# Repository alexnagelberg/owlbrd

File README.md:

# OwlBrd
This board was made to supersede EasyBrd but it has a lot more to it so for cost or complexity, you can pick and choose what you want. The only section needed to drive 8 spools is the core section, ideally with distance sensors as well. Most of these parts can be found [in the US] on Amazon/Digikey and should be widely available and low cost and swappable with different manufacturers, the one exception being the optional TCA9548A breakout which only works with Adafruit's (maybe in future I'll add another row of pins to allow the hiletgo variants, but some workarounds can be done).

All the boards can be soldered either directly down or put down a set of headers so the boards can be removed/replaced. I would maybe take care with the TMC drivers as there's a resistor under each, but you could also solder the resistors on the bottom side if there's concerns of heat/proximity without a header -- probably shouldn't be an issue at all.

## BOM (split by functionality)

### Misc (listed again throughout sections)
 - Dupont male/female headers ([Amazon Affiliate](https://amzn.to/3ps0VLI))
 - Resistors - 1k, 10k, 2.37k, 4.7k used throughout (kit: [Amazon affiliate](https://amzn.to/3c7XxCF))
 - Ceramic capacitors: 0.33uF, 0.1uF used in ERCF/heater (kit: [Amazon affiliate](https://amzn.to/3wbLxqx))
 - Electrolytic capacitors: 100uF 25v used in ERCF/rewinder (kit: [Amazon affiliate](https://amzn.to/3Qs2sNM))
 - JST-XH connectors: 2-pin, 3-pin, 4-pin (kit: [Amazon affiliate](https://amzn.to/3AnAbBp))
 - Screw terminals for power/heater ([Amazon affiliate](https://amzn.to/3T8kE0O))

### Core (Rewind Stepper + Clutches)
- Raspberry Pi Pico ([[Digikey](https://www.digikey.com/en/products/detail/raspberry-pi/SC0915/13624793)] headers are optional)
- BTT TMC2209 x1 ([[Amazon affiliate](https://amzn.to/3prqGvD)] headers encouraged, note that UART is currently wired to the 4th pin and some like FYSETC use the 5th pin. You might be able to resolve this with a jumper on the pins on top?)
- 74HC238 DIP ([Amazon affiliate](https://amzn.to/3PAAPkm)) for clutch (addresses 8 pins using 3 GPIO)
- ULN2803A DIP ([Amazon affiliate](https://amzn.to/3QPcatl)) for clutch (drives 8 clutches using one IC)
- Screw terminal for power
- Resistors: 10k (x1), 1k (x1)
- JST-XH 2 pin female (x8) for clutches
- JST-XH 4 pin female (x2) for rewinder steppers
- Electrolytic capacitor: 100uF 25v

### Distance Sensors
- Adafruit TCA9548A ([Amazon affiliate](https://amzn.to/3wdmtQd) or [adafruit](https://www.adafruit.com/product/2717)) breakout (headers optional, cheaper generics available but one side is slightly wider by like 2.5mm -- might be able to rig something to fit it or could use wires)
- JST-XH 4 pin female (x8) for each sensor

### ERCF
- BTT TMC2209 x2 ([[Amazon affiliate](https://amzn.to/3prqGvD)] headers encouraged, note that UART is currently wired to the 4th pin and some like FYSETC use the 5th pin. You might be able to resolve this with a jumper on the pins on top?)
- L7805CV ([Amazon affiliate](https://amzn.to/3zYoTTM)) 5v linear regulator (probably plenty of substitutions for this but should be readily available -- any 5v regulator with same pinout should work) for supplying 5v power on board
- Resistors: 10k (x2)
- Ceramic capacitors: 0.33uF x1, 0.1uF x1
- Electrolytic capacitors: 100uF 25v (x2)
- JST-XH 3 pin female (x4) for servo, encoder, endstop, and optional neopixel/misc
- JST-XH 4 pin female (x2) for selector/gear steppers

### Heater
- IRLB8721PBF ([Amazon affiliate](https://amzn.to/3A3fAC1)) MOSFET (probably lots of substitutable options but should be readily available)
- BAV99 SMD ([[Amazon affiliate](https://amzn.to/3Pub5Gj)] only surface mount component -- shouldn't be too difficult to solder or need anything special, needed for thermistor)
- Screw terminal (or connector of your choice) for heater
- Resistors: 2.37k (x2), 4.7k (x1)
- Ceramic capacitor: 0.1uF
- JST-XH 2 pin female (for thermistor)

### UART
There's a breakout for UART with power for pi. If you use UART, and don't connect pico to USB, you'll want to put a header and jumper on J29 Ext Power so that it powers the pico from the 5v regulator. Install the 0.33uF and 0.1uF capacitors and L7805CV from ERCF section to get 5v power if needed.

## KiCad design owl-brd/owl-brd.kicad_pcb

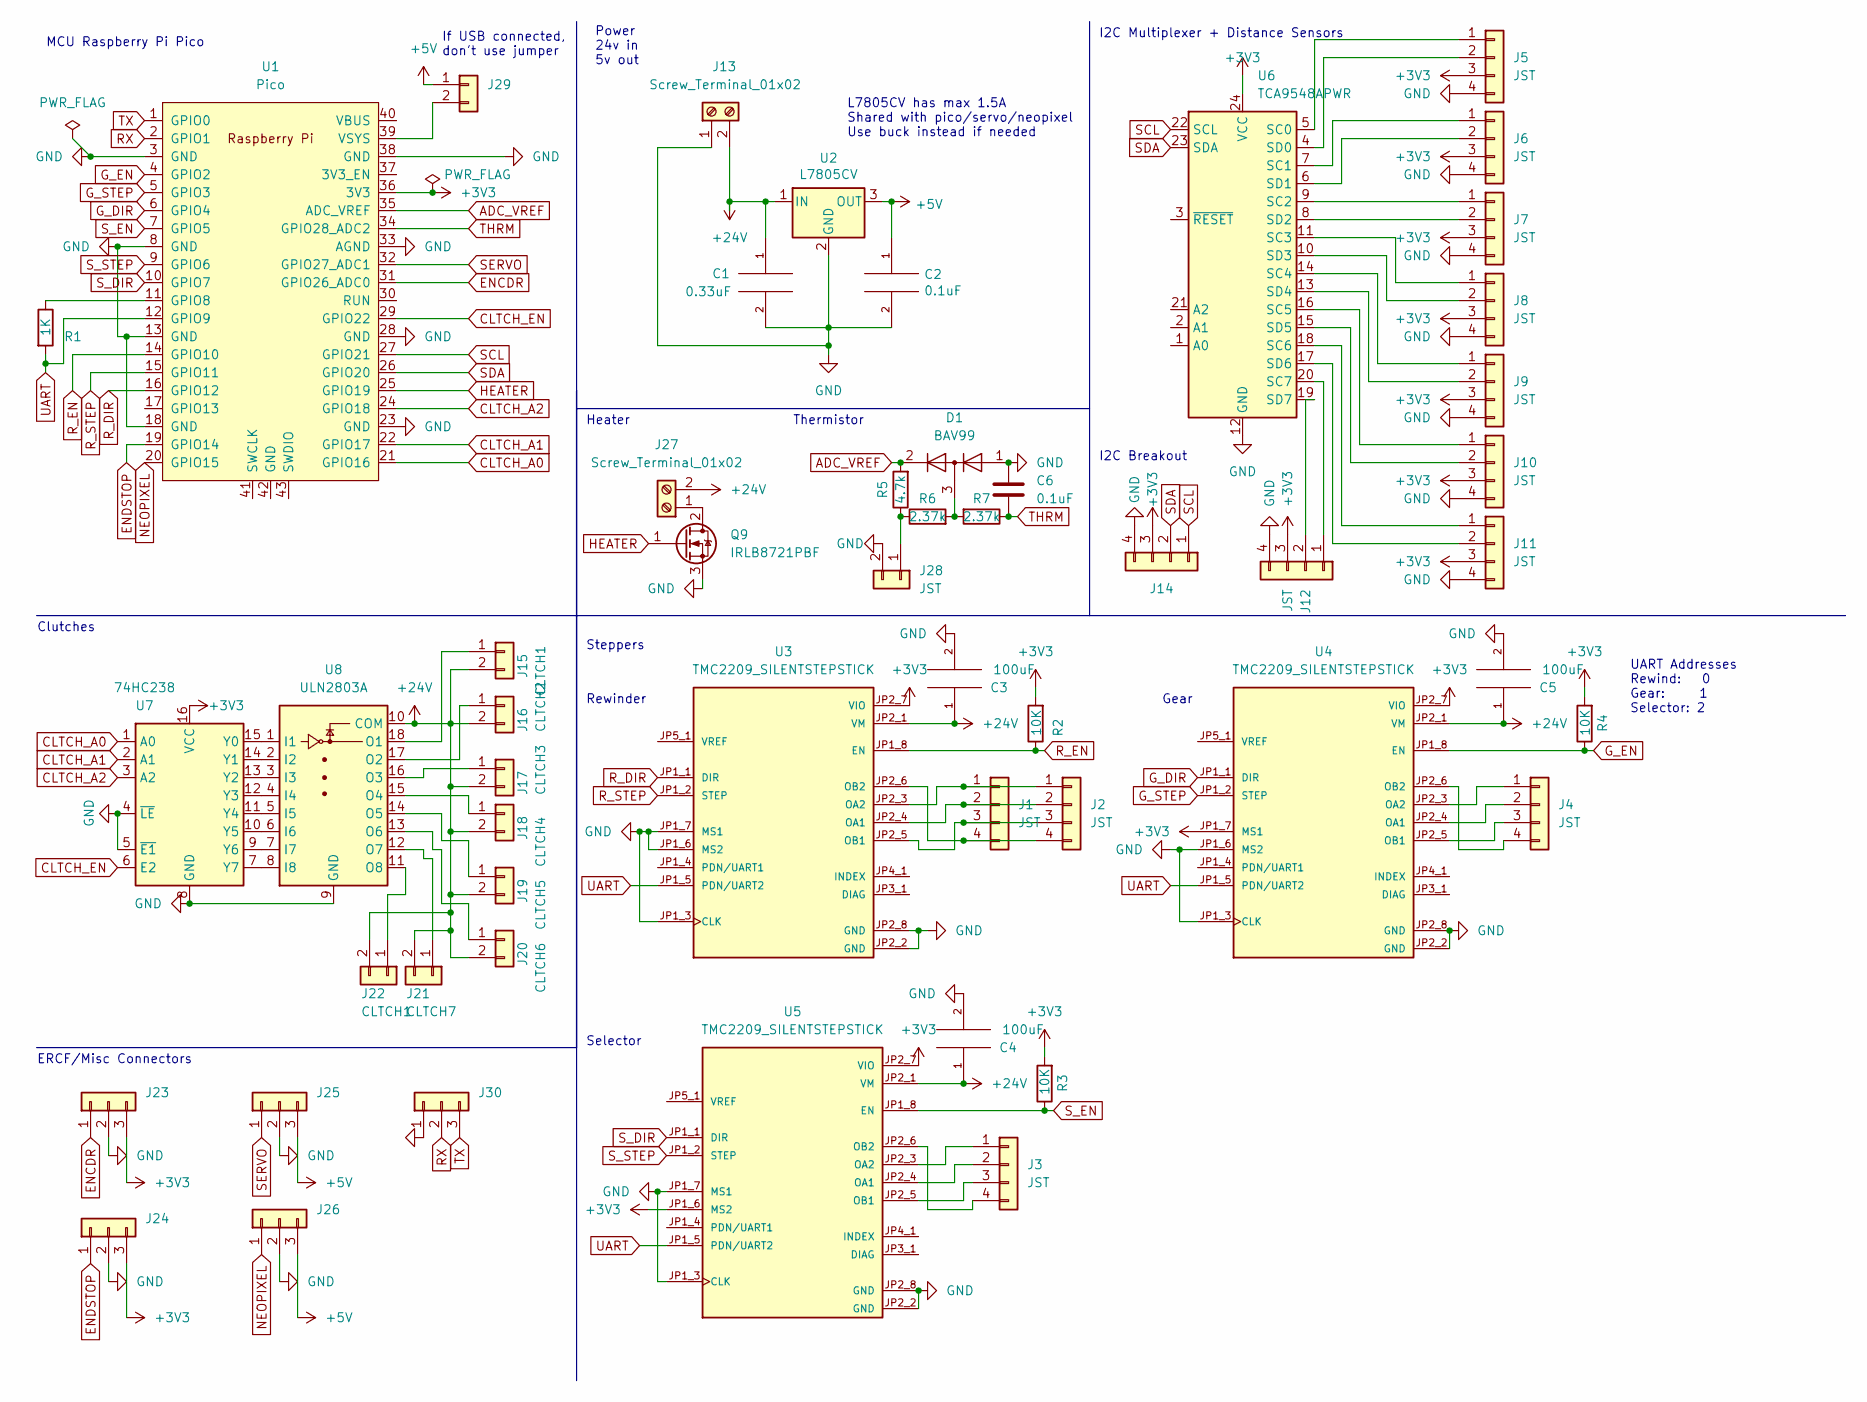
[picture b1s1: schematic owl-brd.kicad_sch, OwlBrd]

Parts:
C1: 0.33uF; C_Disc_D3.0mm_W1.6mm_P2.50mm
C2, C6: 0.1uF; C_Disc_D3.0mm_W1.6mm_P2.50mm
C3, C4, C5: 100uF; CP_Radial_D8.0mm_P3.50mm
D1: BAV99; SOT-23
J1, J2, J3, J4, J5, J6, J7, J8, J9, J10, J11, J12: JST; JST_XH_B4B-XH-A_1x04_P2.50mm_Vertical
J13, J27: Screw_Terminal_01x02; TerminalBlock_bornier-2_P5.08mm
J14, J29, J30: (no value)
J15, J22: CLTCH1; JST_XH_B2B-XH-A_1x02_P2.50mm_Vertical
J16: CLTCH2; JST_XH_B2B-XH-A_1x02_P2.50mm_Vertical
J17: CLTCH3; JST_XH_B2B-XH-A_1x02_P2.50mm_Vertical
J18: CLTCH4; JST_XH_B2B-XH-A_1x02_P2.50mm_Vertical
J19: CLTCH5; JST_XH_B2B-XH-A_1x02_P2.50mm_Vertical
J20: CLTCH6; JST_XH_B2B-XH-A_1x02_P2.50mm_Vertical
J21: CLTCH7; JST_XH_B2B-XH-A_1x02_P2.50mm_Vertical
J23, J24, J25, J26: JST_XH_B3B-XH-A_1x03_P2.50mm_Vertical
J28: JST; JST_XH_B2B-XH-A_1x02_P2.50mm_Vertical
Q9: IRLB8721PBF; TO-220-3_Vertical
R1: 1K; R_Axial_DIN0207_L6.3mm_D2.5mm_P7.62mm_Horizontal
R2, R3, R4: 10K; R_Axial_DIN0207_L6.3mm_D2.5mm_P7.62mm_Horizontal
R5: 4.7k; R_Axial_DIN0207_L6.3mm_D2.5mm_P7.62mm_Horizontal
R6, R7: 2.37k; R_Axial_DIN0207_L6.3mm_D2.5mm_P7.62mm_Horizontal
U1: Pico; RPi_Pico_SMD_TH
U2: L7805CV; TO-220-3_Vertical
U3, U4, U5: TMC2209_SILENTSTEPSTICK; MODULE_TMC2209_SILENTSTEPSTICK; PARTREV v11
U6: TCA9548APWR; TCA9548A
U7: 74HC238; DIP-16_W7.62mm
U8: ULN2803A; DIP-18_W7.62mm

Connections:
+3V3: J5.3, J6.3, J7.3, J8.3, J9.3, J10.3, J11.3, J12.3, J14.3, J23.3, J24.3, R2.2, R3.2, R4.2, U1.36 (3V3), U3.JP2_7 (VIO), U4.JP1_7 (MS1), U4.JP2_7 (VIO), U5.JP1_6 (MS2), U5.JP2_7 (VIO), U6.24 (VCC), U7.16 (VCC)
+5V: C2.1, J25.3, J26.3, J29.1, U2.3 (OUT)
+24V: C1.1, C3.1, C4.1, C5.1, J13.2, J15.2, J16.2, J17.2, J18.2, J19.2, J20.2, J21.2, J22.2, J27.2, U2.1 (IN), U3.JP2_1 (VM), U4.JP2_1 (VM), U5.JP2_1 (VM), U8.10 (COM)
ADC_VREF: D1.2 (A), R5.2, U1.35 (ADC_VREF)
CLTCH_A0: U1.21 (GPIO16), U7.1 (A0)
CLTCH_A1: U1.22 (GPIO17), U7.2 (A1)
CLTCH_A2: U1.24 (GPIO18), U7.3 (A2)
CLTCH_EN: U1.29 (GPIO22), U7.6 (E2)
ENCDR: J23.1, U1.31 (GPIO26_ADC0)
ENDSTOP: J24.1, U1.19 (GPIO14)
G_DIR: U1.6 (GPIO4), U4.JP1_1 (DIR)
G_EN: R4.1, U1.4 (GPIO2), U4.JP1_8 (EN)
G_STEP: U1.5 (GPIO3), U4.JP1_2 (STEP)
HEATER: Q9.1 (G), U1.25 (GPIO19)
NEOPIXEL: J26.1, U1.20 (GPIO15)
unnamed: D1.3 (K), R6.2, R7.2
unnamed: J1.1, J2.1, U3.JP2_3 (OA2)
unnamed: J1.2, J2.2, U3.JP2_4 (OA1)
unnamed: J1.3, J2.3, U3.JP2_5 (OB1)
unnamed: J1.4, J2.4, U3.JP2_6 (OB2)
unnamed: J3.1, U5.JP2_3 (OA2)
unnamed: J3.2, U5.JP2_4 (OA1)
unnamed: J3.3, U5.JP2_5 (OB1)
unnamed: J3.4, U5.JP2_6 (OB2)
unnamed: J4.1, U4.JP2_3 (OA2)
unnamed: J4.2, U4.JP2_4 (OA1)
unnamed: J4.3, U4.JP2_5 (OB1)
unnamed: J4.4, U4.JP2_6 (OB2)
unnamed: J5.1, U6.5 (SC0)
unnamed: J5.2, U6.4 (SD0)
unnamed: J6.1, U6.7 (SC1)
unnamed: J6.2, U6.6 (SD1)
unnamed: J7.1, U6.9 (SC2)
unnamed: J7.2, U6.8 (SD2)
unnamed: J8.1, U6.11 (SC3)
unnamed: J8.2, U6.10 (SD3)
unnamed: J9.1, U6.14 (SC4)
unnamed: J9.2, U6.13 (SD4)
unnamed: J10.1, U6.16 (SC5)
unnamed: J10.2, U6.15 (SD5)
unnamed: J11.1, U6.18 (SC6)
unnamed: J11.2, U6.17 (SD6)
unnamed: J12.1, U6.20 (SC7)
unnamed: J12.2, U6.19 (SD7)
unnamed: J15.1, U8.18 (O1)
unnamed: J16.1, U8.17 (O2)
unnamed: J17.1, U8.16 (O3)
unnamed: J18.1, U8.15 (O4)
unnamed: J19.1, U8.14 (O5)
unnamed: J20.1, U8.13 (O6)
unnamed: J21.1, U8.12 (O7)
unnamed: J22.1, U8.11 (O8)
unnamed: J27.1, Q9.2 (D)
unnamed: J28.1, R5.1, R6.1
unnamed: J29.2, U1.39 (VSYS)
unnamed: R1.1, U1.11 (GPIO8)
unnamed: U7.7 (Y7), U8.8 (I8)
unnamed: U7.9 (Y6), U8.7 (I7)
unnamed: U7.10 (Y5), U8.6 (I6)
unnamed: U7.11 (Y4), U8.5 (I5)
unnamed: U7.12 (Y3), U8.4 (I4)
unnamed: U7.13 (Y2), U8.3 (I3)
unnamed: U7.14 (Y1), U8.2 (I2)
unnamed: U7.15 (Y0), U8.1 (I1)
RX: J30.2, U1.2 (GPIO1)
R_DIR: U1.16 (GPIO12), U3.JP1_1 (DIR)
R_EN: R2.1, U1.14 (GPIO10), U3.JP1_8 (EN)
R_STEP: U1.15 (GPIO11), U3.JP1_2 (STEP)
SCL: J14.1, U1.27 (GPIO21), U6.22 (SCL)
SDA: J14.2, U1.26 (GPIO20), U6.23 (SDA)
SERVO: J25.1, U1.32 (GPIO27_ADC1)
S_DIR: U1.10 (GPIO7), U5.JP1_1 (DIR)
S_EN: R3.1, U1.7 (GPIO5), U5.JP1_8 (EN)
S_STEP: U1.9 (GPIO6), U5.JP1_2 (STEP)
THRM: C6.2, R7.1, U1.34 (GPIO28_ADC2)
TX: J30.3, U1.1 (GPIO0)
UART: R1.2, U1.12 (GPIO9), U3.JP1_5 (PDN/UART2), U4.JP1_5 (PDN/UART2), U5.JP1_5 (PDN/UART2)

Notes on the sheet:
Rewinder
Thermistor
Selector
Power 24v in 5v out
I2C Breakout
Gear
UART Addresses Rewind: 0 Gear: 1 Selector: 2
Clutches
MCU Raspberry Pi Pico
ERCF/Misc Connectors
If USB connected, don't use jumper
L7805CV has max 1.5A Shared with pico/servo/neopixel Use buck instead if needed
I2C Multiplexer + Distance Sensors
Heater
Steppers

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
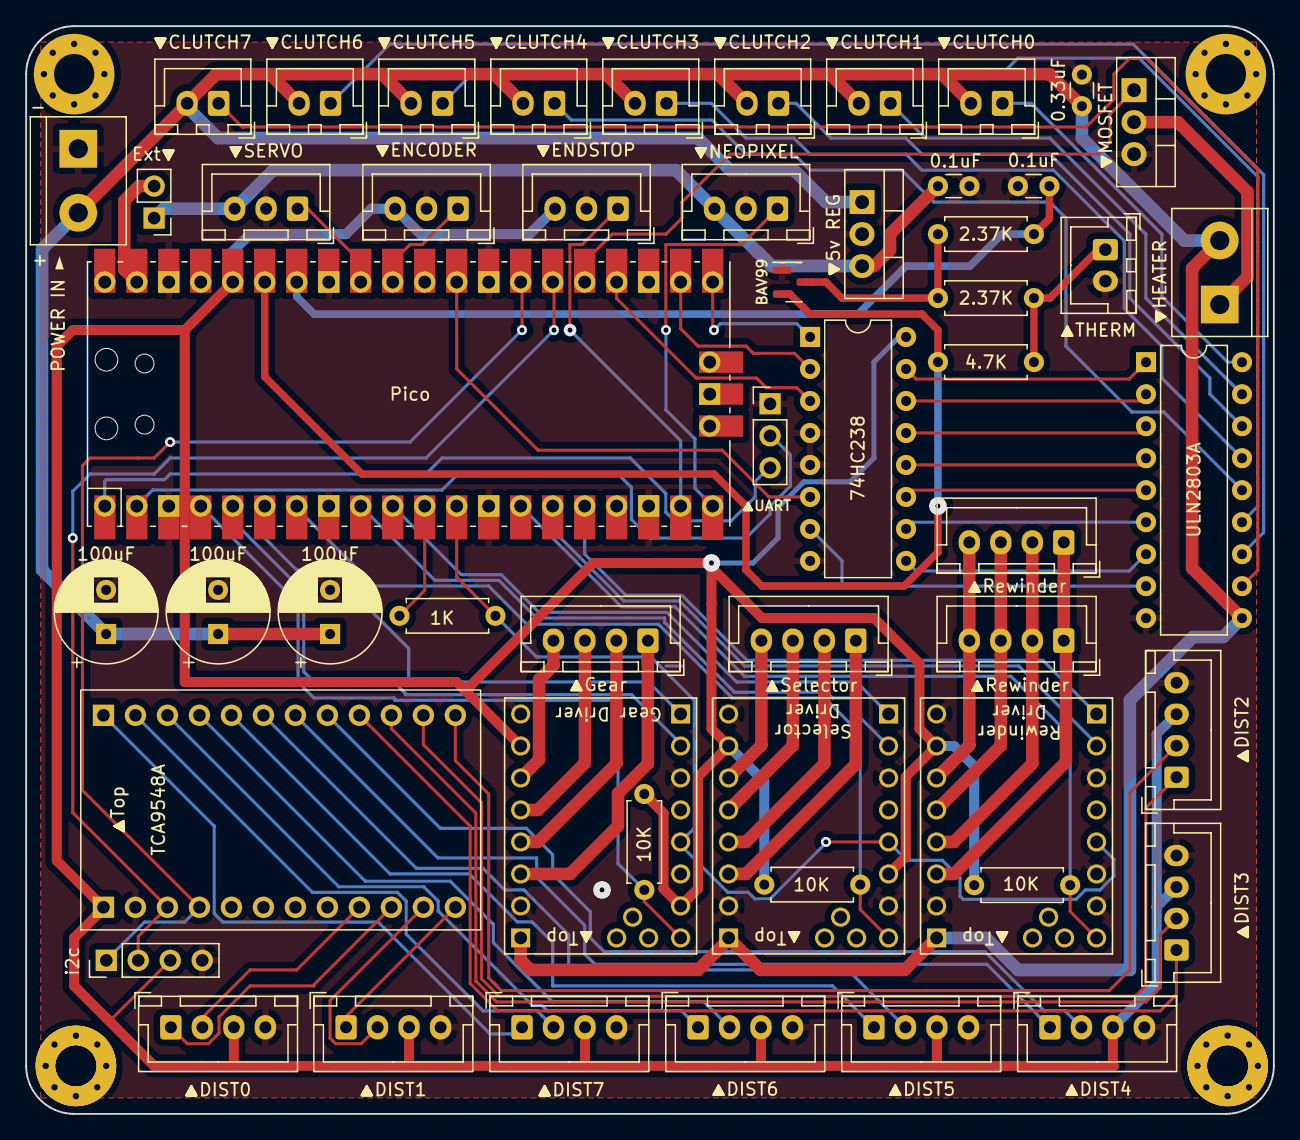
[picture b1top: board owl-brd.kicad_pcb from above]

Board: 2 copper layers, 99.1 x 86.4 mm, 53 parts (0 on the bottom side), 78 nets.

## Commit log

2022-08-17 Initial commit -- splitting to own repo
2022-08-23 - Fix for thermistor mixing vref with 3v3 - Fix footprint for thermistor JST connector - Added enable pin for decoder so that one clutch doesn't have to be on all the time - TODO: rework the CLUTCH p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
2022-08-25 -3d models/images -Flipped mosfet -Changed UART order (and labels to match pico rx/tx), in line with Pi and SKR headers
2022-09-02 DIN mounts for owlbrd
2022-09-18 Revision 1.0.1 - Removed 5v on UART pins (output isn't enough for pi) - Notes/minor cleanup for production

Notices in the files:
owl-brd/owl-brd.kicad_pcb:
MIT License
©2022 Alexander Nagelberg
